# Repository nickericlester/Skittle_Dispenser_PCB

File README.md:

# Skittle_Dispenser_PCB
The repository for my ENGI 301 final project.

This is a PCB for the functions of my Candy Dispenser Project that can be found on my Hackster page at https://www.hackster.io/nickericlester/ir-breakbeam-candy-dispenser-with-zelda-music-c76e65.

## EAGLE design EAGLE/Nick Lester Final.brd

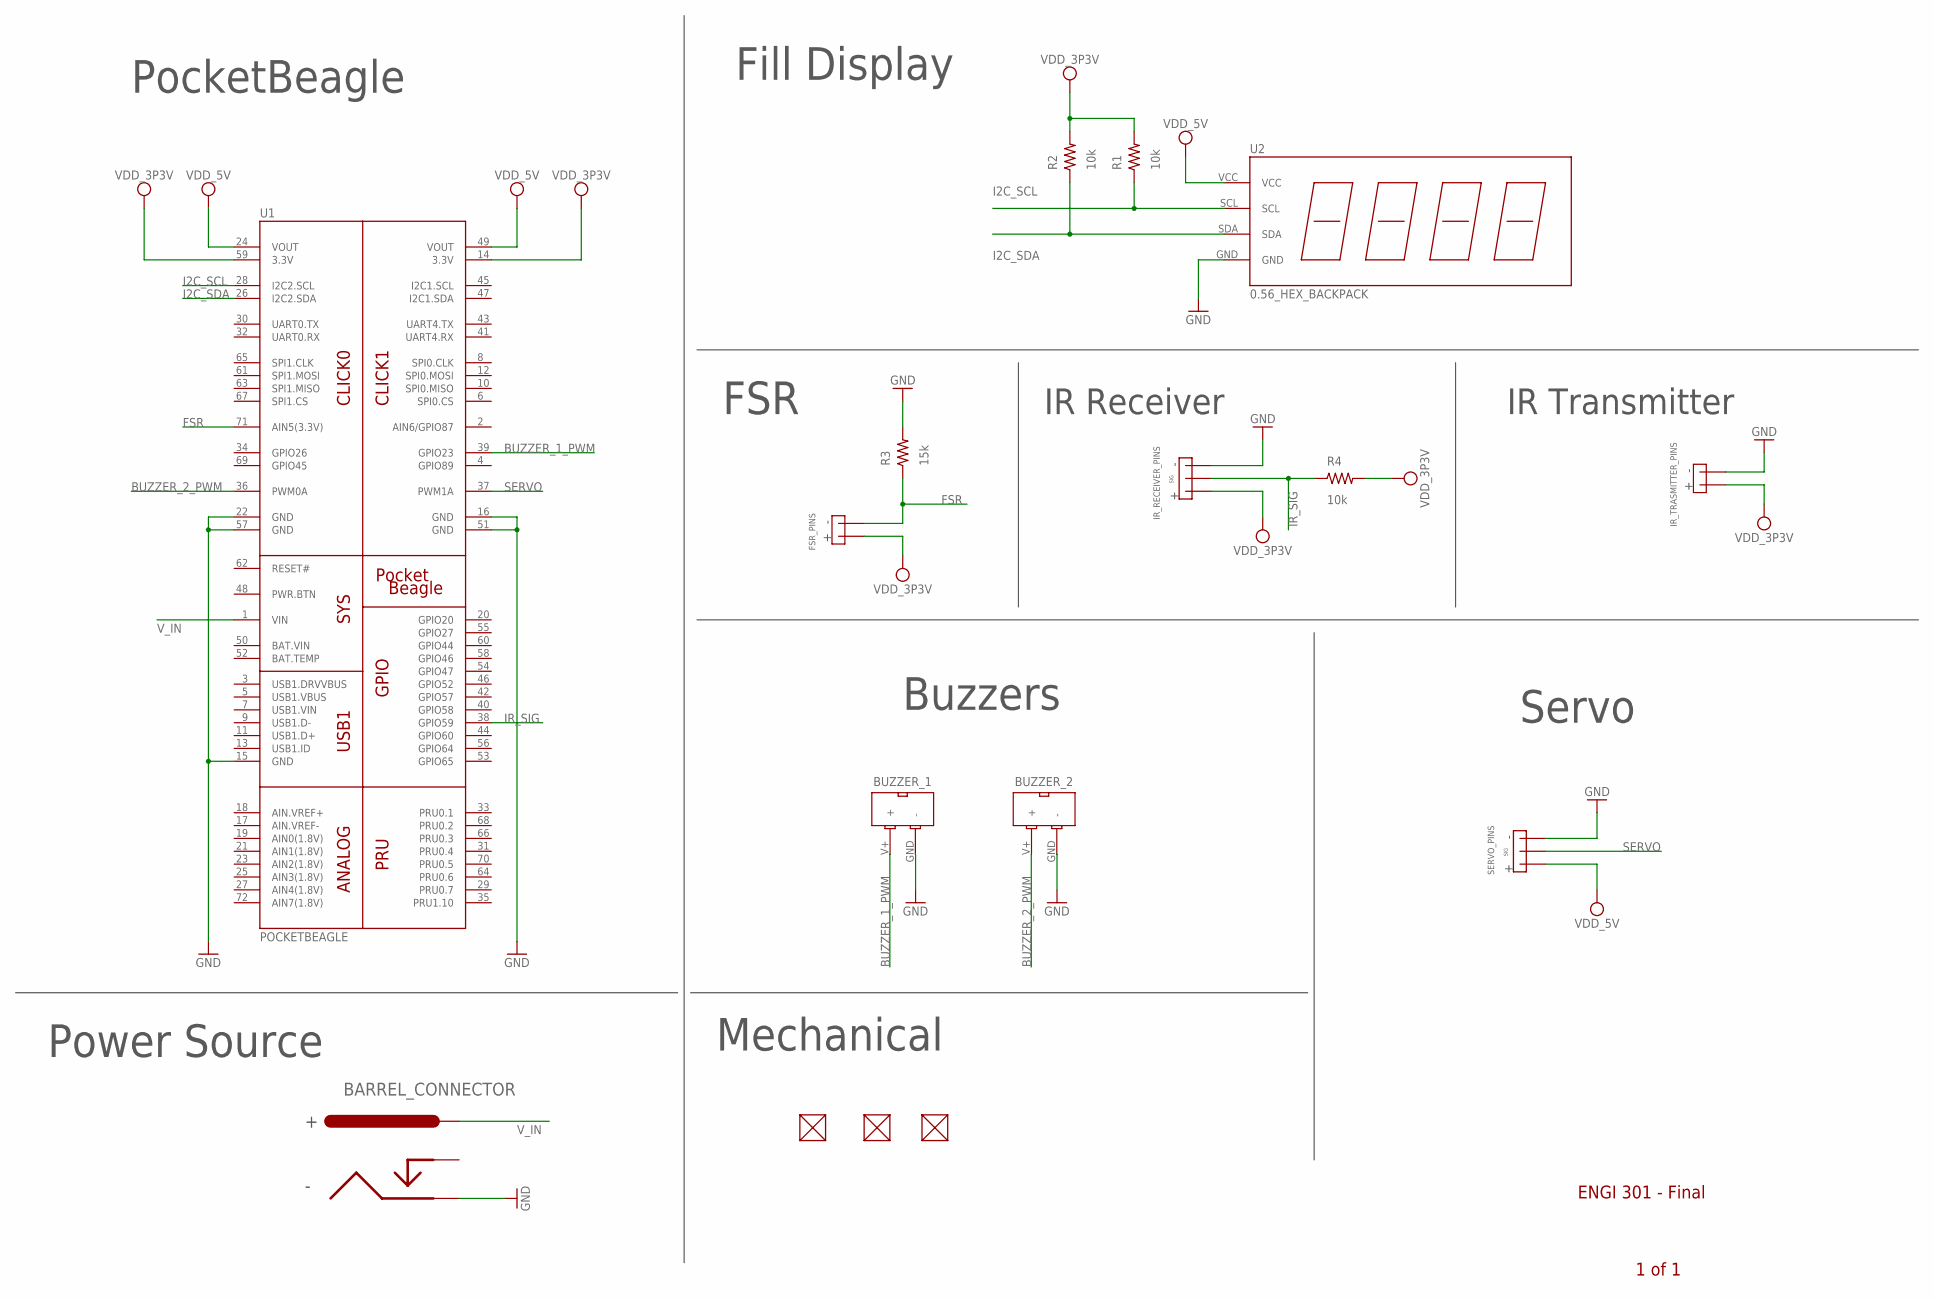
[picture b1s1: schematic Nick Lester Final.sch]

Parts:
BARREL_CONNECTOR: BARREL_CONNECTOR
BUZZER_1, BUZZER_2: PS1240_BUZZER
FSR_PINS: 2_PIN_HEADER
FUD1, FUD2, FUD3: FIDUCIAL; FIDUCIAL_40MIL
IR_RECEIVER_PINS: 3_PIN_HEADER
IR_TRASMITTER_PINS: 2_PIN_HEADER
R1, R2, R4: 10k; R0603
R3: 15k; R0603
SERVO_PINS: 3_PIN_HEADER
U1: POCKETBEAGLE
U2: 0.56_HEX_BACKPACK

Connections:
BAT.VIN: U1.50 (BAT.VIN)
BUZZER_1_PWM: BUZZER_1.V+ (+), U1.39 (GPIO23)
BUZZER_2_PWM: BUZZER_2.V+ (+), U1.36 (PWM0A)
FSR: FSR_PINS.GND, R3.1, U1.71 (AIN5(3.3V))
GND: BARREL_CONNECTOR.GND, BUZZER_1.GND (-), BUZZER_2.GND (-), IR_RECEIVER_PINS.GND, IR_TRASMITTER_PINS.GND, R3.2, SERVO_PINS.GND, U1.15 (GND), U1.16 (GND), U1.22 (GND), U1.51 (GND), U1.57 (GND), U2.GND
I2C_SCL: R1.1, U1.28 (I2C2.SCL), U2.SCL
I2C_SDA: R2.1, U1.26 (I2C2.SDA), U2.SDA
IR_SIG: IR_RECEIVER_PINS.SIG, R4.1, U1.38 (GPIO59)
SERVO: SERVO_PINS.SIG, U1.37 (PWM1A)
VDD_3P3V: FSR_PINS.V+, IR_RECEIVER_PINS.V+, IR_TRASMITTER_PINS.V+, R1.2, R2.2, R4.2, U1.14 (3.3V), U1.59 (3.3V)
VDD_5V: SERVO_PINS.V+, U1.24 (VOUT), U1.49 (VOUT), U2.VCC
V_IN: BARREL_CONNECTOR.V+, U1.1 (VIN)

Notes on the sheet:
PocketBeagle
Fill Display
FSR
IR Receiver
IR Transmitter
Buzzers
Servo
ENGI 301 - Final
1 of 1
Power Source
Mechanical

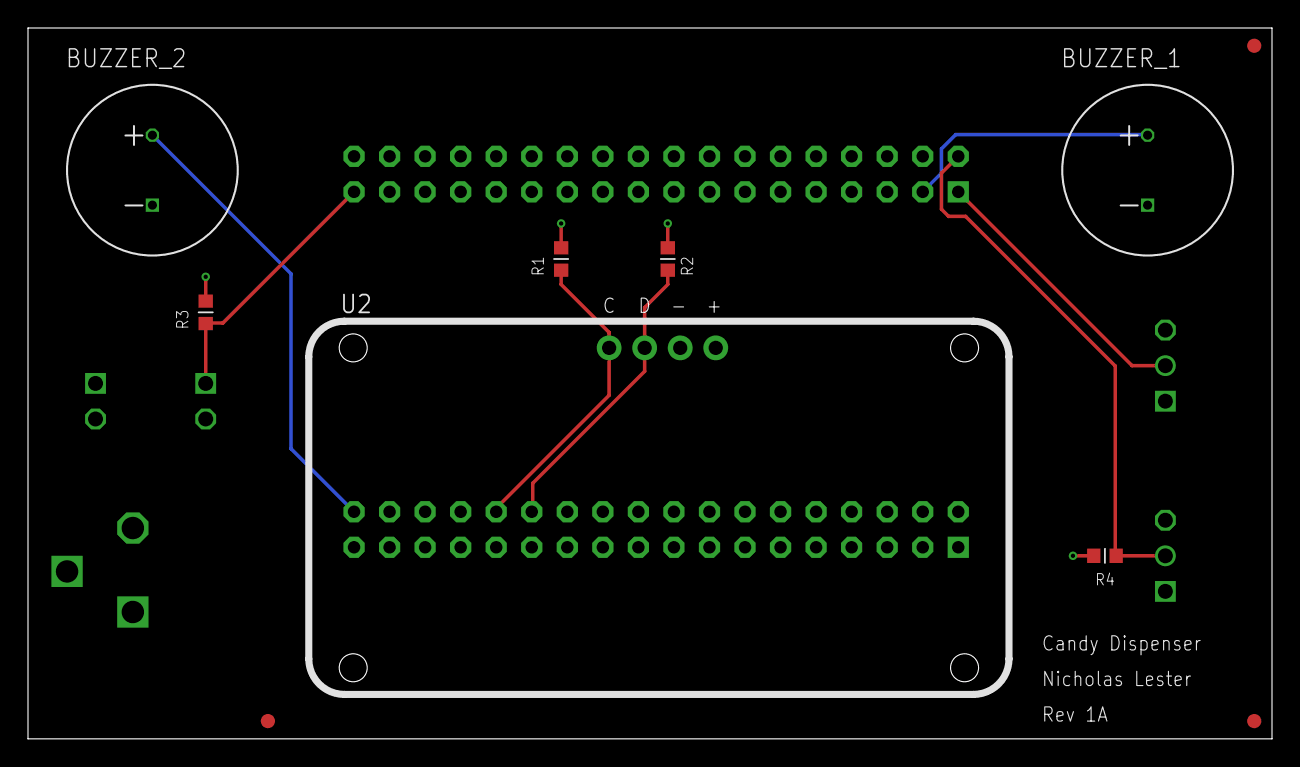
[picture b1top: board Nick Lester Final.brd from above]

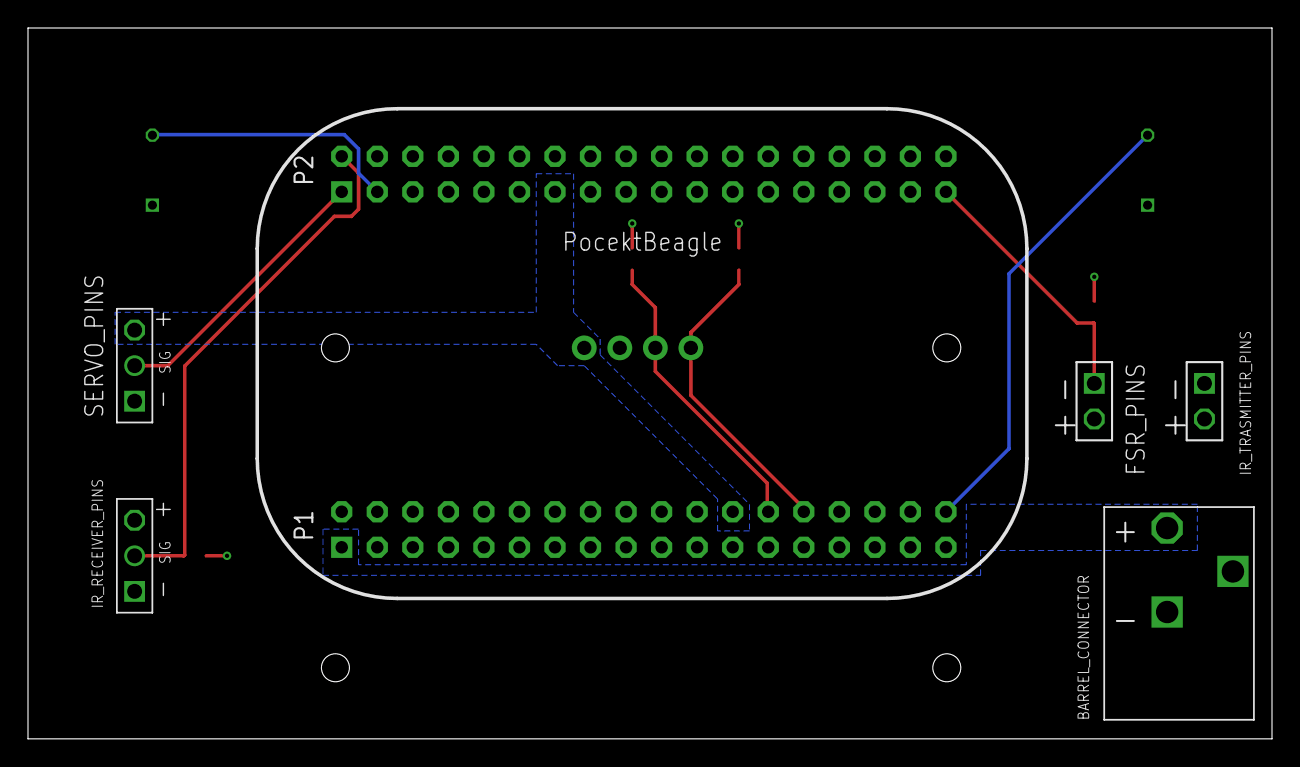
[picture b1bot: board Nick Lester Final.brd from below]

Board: 4 copper layers, 88.9 x 50.8 mm, 16 parts (6 on the bottom side), 11 nets.

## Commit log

2018-12-09 Create empty
